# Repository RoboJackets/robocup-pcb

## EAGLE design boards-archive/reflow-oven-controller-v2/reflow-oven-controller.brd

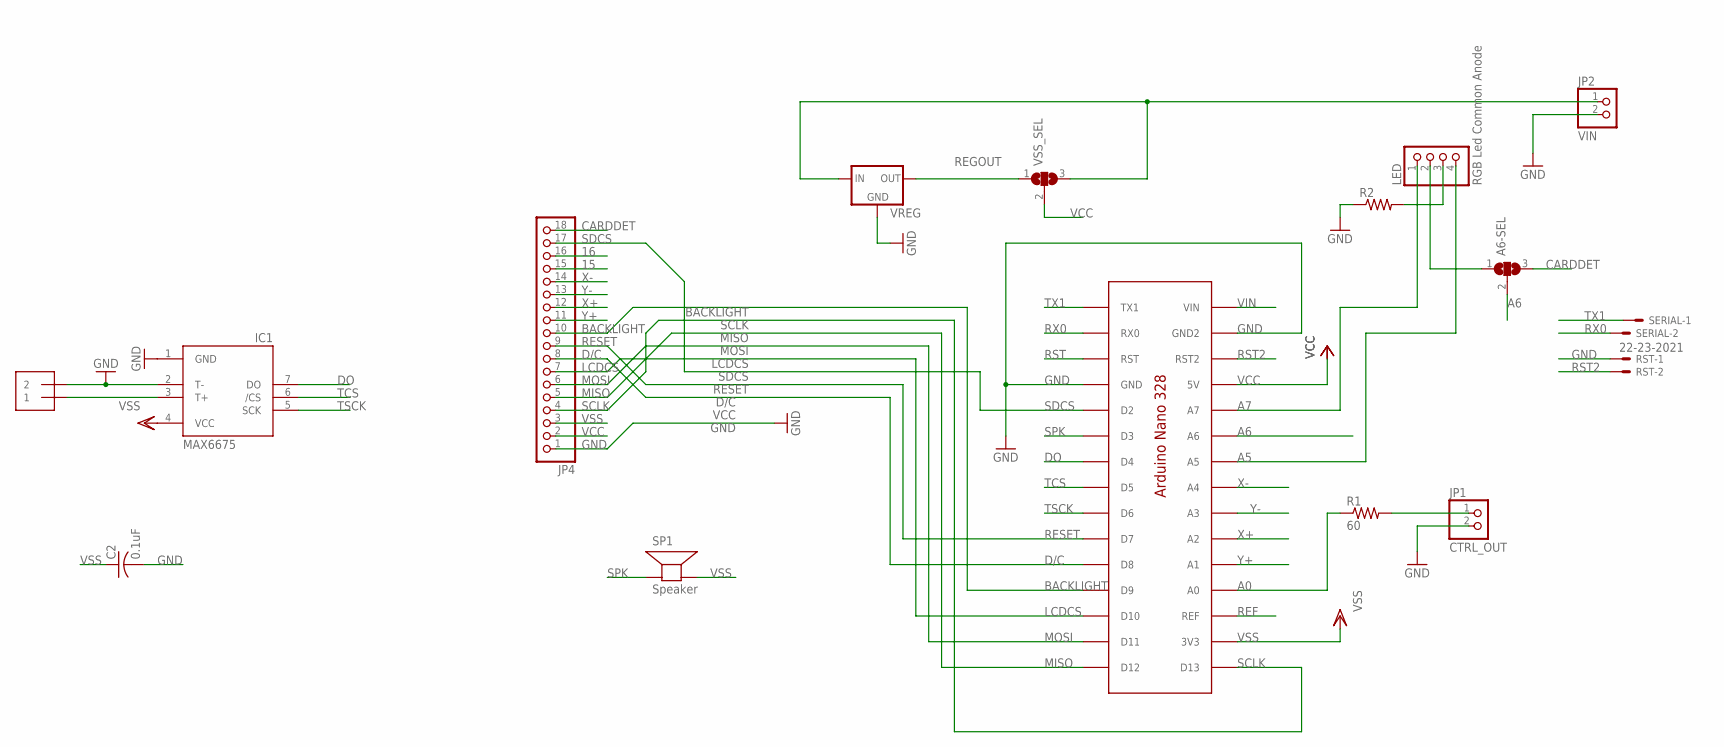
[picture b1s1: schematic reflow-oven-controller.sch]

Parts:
A6-SEL: SJ2W; SJ_2
C2: 0.1uF; C0805K
IC1: MAX6675; SO08
JP1: CTRL_OUT; 1X02/90
JP2: VIN; 1X02/90
JP4: PINHD-1X18; 1X18
LED: RGB Led Common Anode; 1X04
R1: 60; M0805
R2: R-US_R0805; R0805
RST: 22-23-2021
SERIAL: 22-23-2021
SP1: Speaker; PS12
TCOUPLE: 1X2-3.5MM; 3.5MMTERM
U$1: ANANO3.3; ANANO3.0
VREG: 78MXXS; 78SR
VSS_SEL: SJ2W; SJ_2

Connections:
15: JP4.15
16: JP4.16
A0: R1.1, U$1.A0
A5: LED.4, U$1.A5
A6: A6-SEL.2, U$1.A6
A7: LED.1, U$1.A7
BACKLIGHT: JP4.10, U$1.D9
CARDDET: A6-SEL.3, JP4.18
D/C: JP4.8, U$1.D8
DO: IC1.7 (DO), U$1.D4
GND: C2.2, IC1.1 (GND), IC1.2 (T-), JP1.2, JP2.2, JP4.1, R2.1, RST.1, TCOUPLE.2, U$1.GND, U$1.GND2, VREG.GND
LCDCS: JP4.7, U$1.D10
MISO: JP4.5, U$1.D12
MOSI: JP4.6, U$1.D11
unnamed: IC1.3 (T+), TCOUPLE.1
unnamed: A6-SEL.1, LED.2
unnamed: JP1.1, R1.2
unnamed: LED.3, R2.2
REF: U$1.REF
REGOUT: VREG.OUT, VSS_SEL.1
RESET: JP4.9, U$1.D7
RST: U$1.RST
RST2: RST.2, U$1.RST2
RX0: SERIAL.2, U$1.RX0
SCLK: JP4.4, U$1.D13
SDCS: JP4.17, U$1.D2
SPK: SP1.P$1 (+), U$1.D3
TCS: IC1.6 (/CS), U$1.D5
TRANSIN: JP2.1, VREG.IN, VSS_SEL.3
TSCK: IC1.5 (SCK), U$1.D6
TX1: SERIAL.1, U$1.TX1
VCC: JP4.2, U$1.5V, VSS_SEL.2
VIN: U$1.VIN
VSS: C2.1, IC1.4 (VCC), JP4.3, SP1.P$2 (-), U$1.3V3
X+: JP4.12, U$1.A2
X-: JP4.14, U$1.A4
Y+: JP4.11, U$1.A1
Y-: JP4.13, U$1.A3

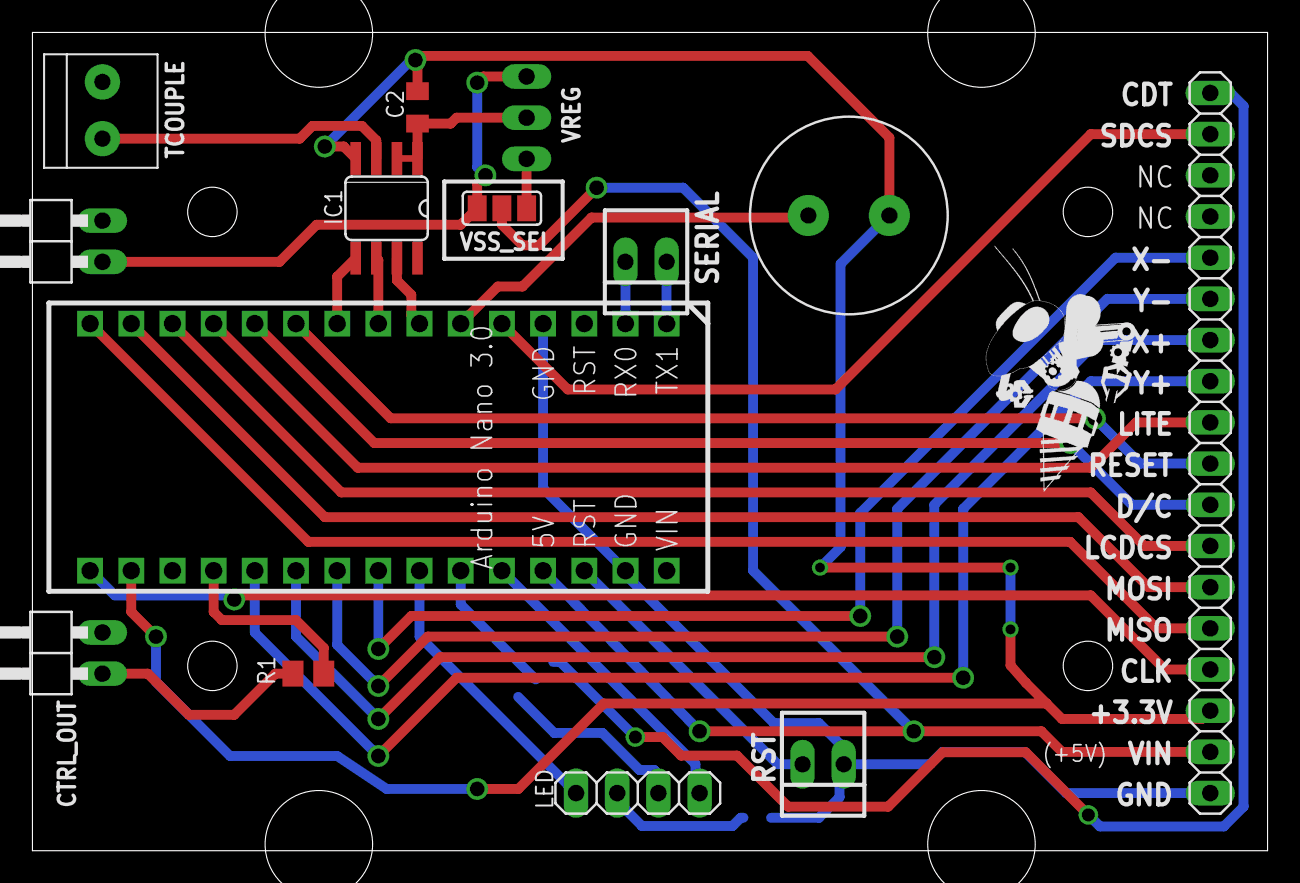
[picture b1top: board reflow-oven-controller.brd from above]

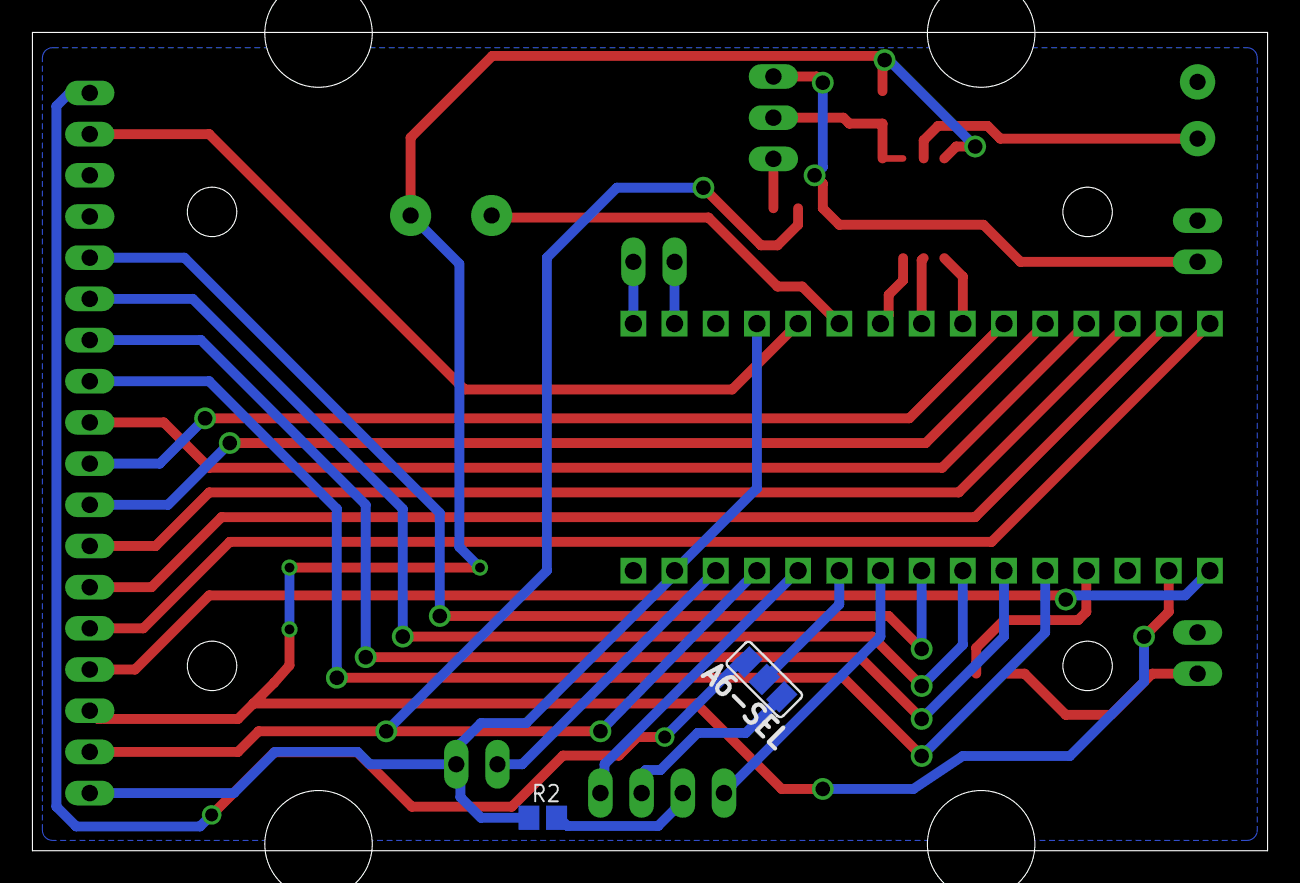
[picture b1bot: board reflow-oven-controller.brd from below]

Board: 2 copper layers, 76.2 x 50.5 mm, 17 parts (2 on the bottom side), 33 nets.

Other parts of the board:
U$2: ROBOBUZZ_0.8X

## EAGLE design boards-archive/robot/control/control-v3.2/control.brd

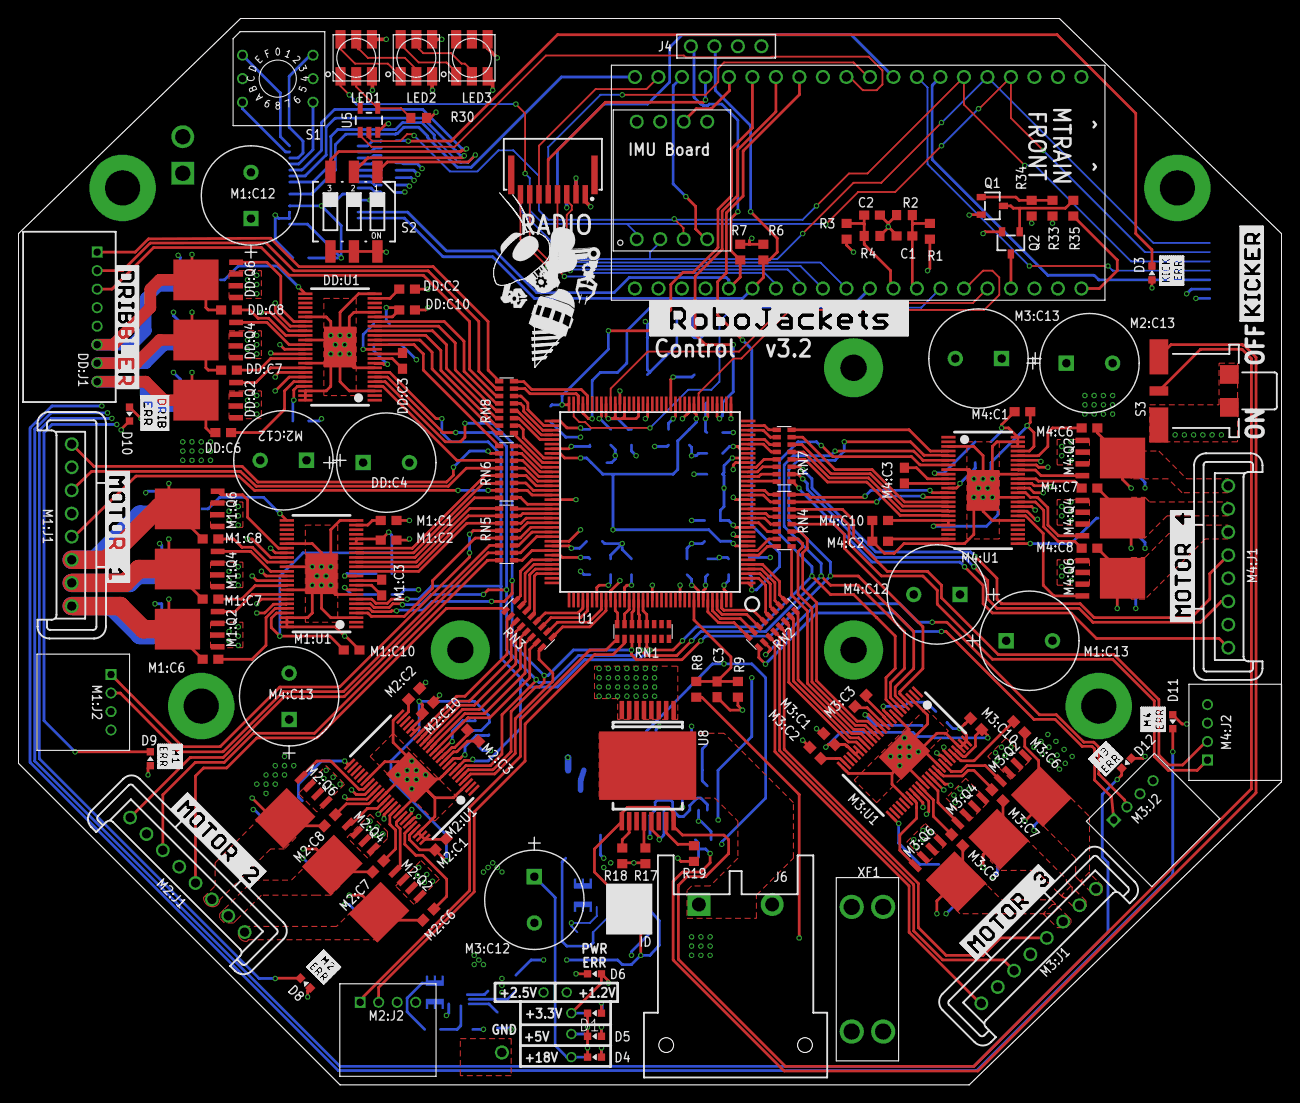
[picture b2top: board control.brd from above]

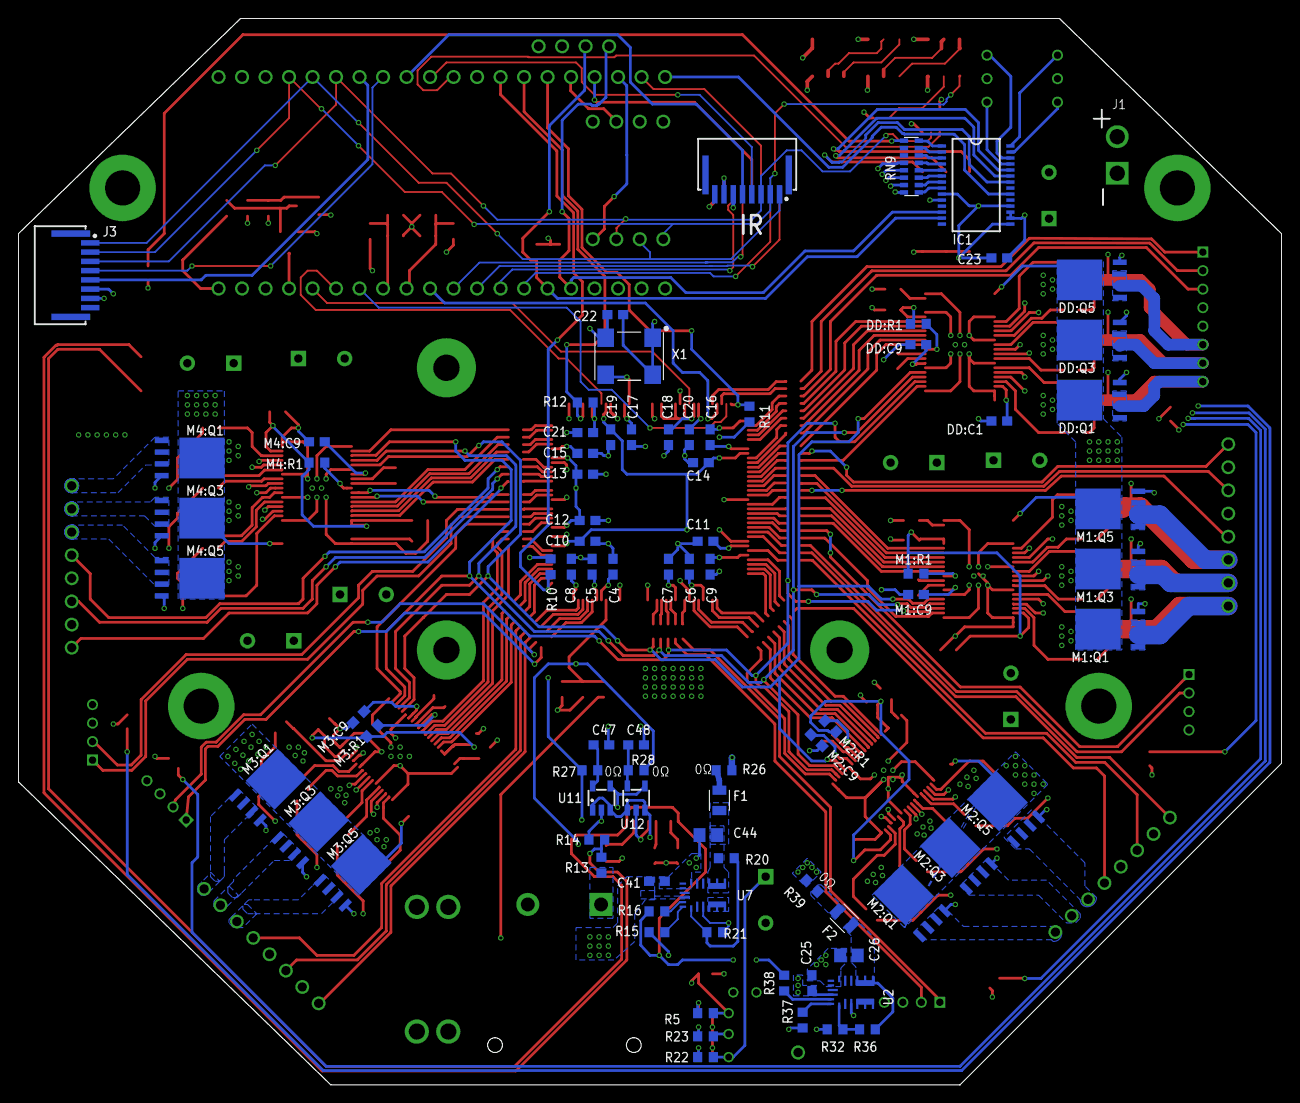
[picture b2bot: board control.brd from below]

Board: 6 copper layers, 136.5 x 115.2 mm, 223 parts (84 on the bottom side), 300 nets.

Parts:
C1: 0.1uF 50V; C0603
C2, C3, C4, C5, C6, C7, C8, C9, C10, C11, C12, C13, C14, C15, C16, C17, C18, C19, C20, C21, C22, C23: 0.1uF; C0603
C25, C41: GRM188R6YA106MA73D; C0603
C26, C44: 22uF 16V; C0805
C47, C48: 1uF; C0603
D1, D4, D5: GREEN; CHIP-LED0603
D3, D6, D8, D9, D10, D11, D12: RED; CHIP-LED0603
DD:C1, DD:C2: 1uF; C0603
DD:C3: 0.022uF 50V; C0603
DD:C4: ECA-1HHG221; CAP_PAN_10X12.5
DD:C6, DD:C7, DD:C8, DD:C10: 0.1uF 50V; C0603
DD:C9: 2.2uF 50V; C0603
DD:J1: 8-PIN_2MM-H; 2MM-8-H
DD:Q1, DD:Q2, DD:Q3, DD:Q4, DD:Q5, DD:Q6: IRFH7545; PQFN_5X6_E
DD:R1: 10k; R0603
DD:U1: DRV8303DCA; TSSOP-48_PAD
F1, F2: 0805L200SLTHYR; FUSC2113X75
IC1: MCP23017-E/SS; SSOP-28
IR: HFW8R-1ST
J1: 2-PIN-KICKERS; B2P_SMALL
J3: HFW8R-1ST
J4: 4-PIN-HEADER
J6: DF22-2; DF22-2-H
KIT1: MTRAIN; MTRAIN-KIT
KIT2: IMUIMU-KIT; IMU-KIT
LED1, LED2, LED3: APA102C-5050; APA102_5050
M1:C1, M1:C2, M2:C1, M2:C2, M3:C1, M3:C2, M4:C1, M4:C2: 1uF; C0603
M1:C3, M2:C3, M3:C3, M4:C3: 0.022uF 50V; C0603
M1:C6, M1:C7, M1:C8, M1:C10, M2:C6, M2:C7, M2:C8, M2:C10, M3:C6, M3:C7, M3:C8, M3:C10, M4:C6, M4:C7, M4:C8, M4:C10: 0.1uF 50V; C0603
M1:C9, M2:C9, M3:C9, M4:C9: 2.2uF 50V; C0603
M1:C12, M1:C13, M2:C12, M2:C13, M3:C12, M3:C13, M4:C12, M4:C13: ECA-1HHG221; CAP_PAN_10X12.5
M1:J1, M2:J1, M3:J1, M4:J1: MKS-1658
M1:J2, M2:J2, M3:J2, M4:J2: 4-PIN_2MM-H; 2MM-4-H
M1:Q1, M1:Q2, M1:Q3, M1:Q4, M1:Q5, M1:Q6, M2:Q1, M2:Q2, M2:Q3, M2:Q4, M2:Q5, M2:Q6, M3:Q1, M3:Q2, M3:Q3, M3:Q4, M3:Q5, M3:Q6, M4:Q1, M4:Q2, M4:Q3, M4:Q4, M4:Q5, M4:Q6: IRFH7545; PQFN_5X6_E
M1:R1, M2:R1, M3:R1, M4:R1: 10k; R0603
M1:U1, M2:U1, M3:U1, M4:U1: DRV8303DCA; TSSOP-48_PAD
Q1, Q2: BSS806NH6327XTSA1; SOT-23-3
R1: 68k 1%; R0603
R2, R3, R4: 10k 1%; R0603
R5, R18, R19, R22, R23: 1k; R0603
R6, R7, R10, R12: 4.7k; R0603
R8: 68k; R0603
R9, R17, R33: 10k; R0603
R11: 330; R0603
R13: 270k; R0603
R14, R34, R35: 100k; R0603
R15: 43.2k; R0603
R16, R38: 150k; R0603
R20, R36: 160k 1%; R0603
R21: 30.1k 1%; R0603
R26, R27, R28, R39: 0; R0603
R30: 50k; R0603
R32: 51.0k 1%; R0603
R37: 29.4k; R0603
RADIO: HFW8R-1ST
RN1, RN2, RN3, RN4, RN5, RN6, RN7, RN8, RN9: 330; RA-8_2506
S1: 94HCB16T; HEX
S2: 219-03; CTS-219-03
S3: 34EWMSP12M6RT
U1: XC3S250E-4TQG144C; TQFP144
U2, U7: MPM3620GQV-P
U5: SN74AHC1G125; SOT23-5
U8: VND5E006ASPTR-E; POWERSO-16
U11: MCP1824T-1202E/OT; SOT-23-5
U12: MCP1824T-2502E/OT; SOT-23-5
U$1: ERR-DRIB
U$2: ROBOJACKETS
U$3: MOTOR-1
U$4: DRIBBLER
U$5: MOTOR-2
U$6: MOTOR-3
U$7: MOTOR-4
U$8: ERR-M1
U$9: KICKER
U$11: ROBOBUZZ_1.0X2
U$12: ERR-M2
U$13: ERR-M3
U$14: ERR-M4
U$15: ERR-KICK
X1: ASV-18.432MHZ-EJ-T; ASV
XF1: 30A; 3557-2

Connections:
5V-LED: D5.A, R23.2
5V-LED1: D1.A, R5.2
18.5V-LED: D4.A, R22.1
!CS!-DOT: KIT1.P$11, U5.1
!CS!-FPGA: KIT1.P$31, U1.69
!CS!-ICM: KIT1.P$18, KIT2.4
!CS!-IR: IR.4, KIT1.P$10
!CS!-KICK: J3.4, KIT1.P$8
!CS!-RAD0: KIT1.P$17, RADIO.5
!RST!-IR: IR.5, KIT1.P$9
!RST!-KICK: J3.5, KIT1.P$7
!RST!-NETWORK: KIT1.!RST, Q2.3
!RST!-RADIO: KIT1.P$19, RADIO.6
!RST!_CTRL: Q1.3, Q2.1, R35.1
+1.2V: C6.1, C10.1, C14.1, C19.1, R27.2, U1.9, U1.45, U1.80, U1.115
+1.2V-PRE: C47.1, R27.1, U11.5
+2.5V: C4.1, C9.1, C15.1, C20.1, R10.2, R11.2, R28.2, U1.30, U1.65, U1.102, U1.137
+2.5V-PRE: C48.1, R28.1, U12.5
+3.3V: C5.1, C7.1, C8.1, C11.1, C12.1, C13.1, C16.1, C17.1, C18.1, C21.1, C22.1, C23.1, D3.A, D6.A, D8.A, D9.A, D10.A, D11.A, D12.A, DD:C1.1, DD:C10.1, DD:R1.1, DD:U1.19, DD:U1.45, IC1.9, IC1.15, IC1.18, IR.6, J3.7, J4.2, KIT2.8, R5.1, R6.2, R7.2, R12.1, R33.2, R39.2, U1.13, U1.28, U1.42, U1.49, U1.57, U1.60, U1.62, U1.64, U1.79, U1.100, U1.121, U1.138, U1.143, U5.5, U11.1, U11.3, U12.1, U12.3, X1.1, X1.4
+3.3V-FUSE: C26.1, F2.1, R36.2, U2.789
+5V: DD:J1.5, KIT1.VIN, LED1.1, LED2.1, LED3.1, M1:J1.4, M1:J2.4, M2:J1.4, M2:J2.4, M3:J1.4, M3:J2.4, M4:J1.4, M4:J2.4, R3.1, R23.1, R26.2, RADIO.1
+5V-FUSE: C44.1, F1.1, R20.2, U7.789
+18.5V: C25.1, C41.1, DD:C4.1, DD:Q1.5678, DD:Q3.5678, DD:Q5.5678, DD:U1.25, M1:C12.1, M1:C13.1, M1:Q1.5678, M1:Q3.5678, M1:Q5.5678, M1:U1.25, M2:C12.1, M2:C13.1, M2:Q1.5678, M2:Q3.5678, M2:Q5.5678, M2:U1.25, M3:C12.1, M3:C13.1, M3:Q1.5678, M3:Q3.5678, M3:Q5.5678, M3:U1.25, M4:C12.1, M4:C13.1, M4:Q1.5678, M4:Q3.5678, M4:Q5.5678, M4:U1.25, R1.1, R8.1, R22.2, U2.16, U7.16, XF1.3, XF1.4
AAM: R15.2, U7.18
AAM1: R37.2, U2.18
BATT-FPGA: C3.1, R8.2, R9.1, U1.136
BATT_PWR_AVAIL: Q1.1, R33.1, R34.2
CS1: R18.2, U8.10
CS2: R19.2, U8.15
CS-DIS: R17.2, U8.12
DD-!CS: DD:U1.4, RN6.11
DD-A-H: DD:U1.13, RN6.9
DD-A-L: DD:U1.14, RN8.16
DD-B-H: DD:U1.15, RN8.15
DD-B-L: DD:U1.16, RN8.14
DD-C-H: DD:U1.17, RN8.13
DD-C-L: DD:U1.18, RN8.12
DD-H1: DD:J1.3, RN8.11
DD-H2: DD:J1.2, RN8.10
DD-H3: DD:J1.1, RN8.9
DD:AVDD: DD:C2.1, DD:U1.23
DD:BST-A: DD:C6.1, DD:U1.44
DD:BST-B: DD:C7.1, DD:U1.39
DD:BST-C: DD:C8.1, DD:U1.34
DD:CP1: DD:C3.1, DD:U1.10
DD:CP2: DD:C3.2, DD:U1.11
DD:EN-GATE: DD:R1.2, DD:U1.12
DD:GH-A: DD:Q1.4, DD:U1.43
DD:GH-B: DD:Q3.4, DD:U1.38
DD:GH-C: DD:Q5.4, DD:U1.33
DD:GL-A: DD:Q2.4, DD:U1.41
DD:GL-B: DD:Q4.4, DD:U1.36
DD:GL-C: DD:Q6.4, DD:U1.31
DD:GVDD: DD:C9.1, DD:U1.9
DD:PHASE-A: DD:C6.2, DD:J1.8, DD:Q1.1, DD:Q1.2, DD:Q1.3, DD:Q2.5678, DD:U1.42
DD:PHASE-B: DD:C7.2, DD:J1.7, DD:Q3.1, DD:Q3.2, DD:Q3.3, DD:Q4.5678, DD:U1.37
DD:PHASE-C: DD:C8.2, DD:J1.6, DD:Q5.1, DD:Q5.2, DD:Q5.3, DD:Q6.5678, DD:U1.32
DIP-1: IC1.22, S2.1
DIP-2: IC1.23, S2.2
DIP-3: IC1.24, S2.3
DOT-CLK-1: LED1.5, R30.2, U5.4
DOT-CLK-1-2: LED1.2, LED2.5
DOT-CLK-2-3: LED2.2, LED3.5
DOT-MOSI-1-2: LED1.3, LED2.4
DOT-MOSI-2-3: LED2.3, LED3.4
EN: R16.2, U7.17
EN1: R38.2, U2.17
EN-PWR: R16.1, R38.1, S3.2, U8.9, U8.16
EN-PWR-PRE: R13.1, R14.2, S3.1
FB: R20.1, R21.2, U7.1
FB1: R32.2, R36.1, U2.1
FPGA-CLK: U1.50, X1.3
FPGA-DONE: KIT1.P$15, R11.1, U1.72
FPGA-INIT: KIT1.P$14, R12.2, U1.40
FPGA-PROG: KIT1.P$13, R10.1, U1.1
GND: C1.2, C2.2, C3.2, C4.2, C5.2, C6.2, C7.2, C8.2, C9.2, C10.2, C11.2, C12.2, C13.2, C14.2, C15.2, C16.2, C17.2, C18.2, C19.2, C20.2, C21.2, C22.2, C23.2, C25.2, C26.2, C41.2, C44.2, C47.2, C48.2, D1.C, D4.C, D5.C, DD:C1.2, DD:C2.2, DD:C4.2, DD:C9.2, DD:C10.2, DD:J1.4, DD:Q2.1, DD:Q2.2, DD:Q2.3, DD:Q4.1, DD:Q4.2, DD:Q4.3, DD:Q6.1, DD:Q6.2, DD:Q6.3, DD:U1.3, DD:U1.8, DD:U1.20, DD:U1.24, DD:U1.30, DD:U1.35, DD:U1.40, DD:U1.46, DD:U1.47, DD:U1.48, DD:U1.PAD, IC1.10, IC1.16, IC1.17, IR.7, J1.1, J3.6, J4.1, J6.2, KIT1.GND, KIT2.5, LED1.6, LED2.6, LED3.6, M1:C1.2, M1:C2.2, M1:C9.2, M1:C10.2, M1:C12.2, M1:C13.2, M1:J1.2, M1:J2.3, M1:Q2.1, M1:Q2.2, M1:Q2.3, M1:Q4.1, M1:Q4.2, M1:Q4.3, M1:Q6.1, M1:Q6.2, M1:Q6.3, M1:U1.3, M1:U1.8, M1:U1.24, M1:U1.30, M1:U1.35, M1:U1.40, M1:U1.46, M1:U1.47, M1:U1.48, M1:U1.PAD, M2:C1.2, M2:C2.2, M2:C9.2, M2:C10.2, M2:C12.2, M2:C13.2, M2:J1.2, M2:J2.3, M2:Q2.1, M2:Q2.2, M2:Q2.3, M2:Q4.1, M2:Q4.2, M2:Q4.3, M2:Q6.1, M2:Q6.2, M2:Q6.3, M2:U1.3, M2:U1.8, M2:U1.24, M2:U1.30, M2:U1.35, M2:U1.40, M2:U1.46, M2:U1.47, M2:U1.48, M2:U1.PAD, M3:C1.2, M3:C2.2, M3:C9.2, M3:C10.2, M3:C12.2, M3:C13.2, M3:J1.2, M3:J2.3, M3:Q2.1, M3:Q2.2, M3:Q2.3, M3:Q4.1, M3:Q4.2, M3:Q4.3, M3:Q6.1, M3:Q6.2, M3:Q6.3, M3:U1.3, M3:U1.8, M3:U1.24, M3:U1.30, M3:U1.35, M3:U1.40, M3:U1.46, M3:U1.47, M3:U1.48, M3:U1.PAD, M4:C1.2, M4:C2.2, M4:C9.2, M4:C10.2, M4:C12.2, M4:C13.2, M4:J1.2, M4:J2.3, M4:Q2.1, M4:Q2.2, M4:Q2.3, M4:Q4.1, M4:Q4.2, M4:Q4.3, M4:Q6.1, M4:Q6.2, M4:Q6.3, M4:U1.3, M4:U1.8, M4:U1.24, M4:U1.30, M4:U1.35, M4:U1.40, M4:U1.46, M4:U1.47, M4:U1.48, M4:U1.PAD, Q1.2, Q2.2, R2.2, R4.2, R9.2, R14.1, R15.1, R17.1, R18.1, R19.1, R21.1, R30.1, R32.1, R34.1, R37.1, RADIO.2, S1.C1, S1.C2, S2.4, S2.5, S2.6, S3.3, S3.LEG1, S3.LEG3, U1.11, U1.19, U1.27, U1.37, U1.46, U1.55, U1.61, U1.73, U1.90, U1.99, U1.118, U1.127, U1.133, U2.3, U2.12, U2.13, U2.14, U5.3, U7.3, U7.12, U7.13, U7.14, U8.13, U11.2, U12.2, X1.2
GPB0: IC1.1, RN9.8
GPB1: IC1.2, RN9.7
GPB2: IC1.3, RN9.6
GPB3: IC1.4, RN9.5
GPB4: IC1.5, RN9.4
GPB5: IC1.6, RN9.3
GPB6: IC1.7, RN9.2
GPB7: IC1.8, RN9.1
HEX-0: IC1.28, S1.1
HEX-1: IC1.25, S1.2
HEX-2: IC1.27, S1.4
HEX-3: IC1.26, S1.8
INT-ICM: KIT1.P$16, KIT2.6
INT-IO: IC1.20, KIT1.P$20
INT-RAD0: KIT1.P$30, RADIO.4
LED-DD: D10.C, RN9.16
LED-KICK: D3.C, RN9.9
LED-M1: D9.C, RN9.15
LED-M2: D8.C, RN9.14
LED-M3: D12.C, RN9.13
LED-M4: D11.C, RN9.12
M1-!CS: M1:U1.4, RN5.13
M1-A-H: M1:U1.15, RN5.9
M1-A-L: M1:U1.16, RN6.16
M1-B-H: M1:U1.13, RN5.11
M1-B-L: M1:U1.14, RN5.10
M1-C-H: M1:U1.17, RN6.14
M1-C-L: M1:U1.18, RN6.13
M1-ENC-A: M1:J2.2, RN5.14
M1-ENC-B: M1:J2.1, RN5.12
M1-H1: M1:J1.1, RN6.10
M1-H2: M1:J1.3, RN6.12
M1-H3: M1:J1.5, RN6.15
M1:+3.3V: M1:C1.1, M1:C10.1, M1:R1.1, M1:U1.19, M1:U1.20, M1:U1.45
M1:AVDD: M1:C2.1, M1:U1.23
M1:BST-A: M1:C6.1, M1:U1.44
M1:BST-B: M1:C7.1, M1:U1.39
M1:BST-C: M1:C8.1, M1:U1.34
M1:CP1: M1:C3.1, M1:U1.10
M1:CP2: M1:C3.2, M1:U1.11
M1:EN-GATE: M1:R1.2, M1:U1.12
M1:GH-A: M1:Q1.4, M1:U1.43
M1:GH-B: M1:Q3.4, M1:U1.38
M1:GH-C: M1:Q5.4, M1:U1.33
M1:GL-A: M1:Q2.4, M1:U1.41
M1:GL-B: M1:Q4.4, M1:U1.36
M1:GL-C: M1:Q6.4, M1:U1.31
M1:GVDD: M1:C9.1, M1:U1.9
M1:PHASE-A: M1:C7.2, M1:J1.7, M1:Q3.1, M1:Q3.2, M1:Q3.3, M1:Q4.5678, M1:U1.37
M1:PHASE-B: M1:C6.2, M1:J1.8, M1:Q1.1, M1:Q1.2, M1:Q1.3, M1:Q2.5678, M1:U1.42
M1:PHASE-C: M1:C8.2, M1:J1.6, M1:Q5.1, M1:Q5.2, M1:Q5.3, M1:Q6.5678, M1:U1.32
M2-!CS: M2:U1.4, RN3.16
M2-A-H: M2:U1.15, RN3.13
M2-A-L: M2:U1.16, RN3.12
M2-B-H: M2:U1.13, RN3.15
M2-B-L: M2:U1.14, RN3.14
M2-C-H: M2:U1.17, RN3.11
M2-C-L: M2:U1.18, RN3.10
M2-ENC-A: M2:J2.2, RN1.10
M2-ENC-B: M2:J2.1, RN1.9
M2-H1: M2:J1.1, RN5.15
M2-H2: M2:J1.3, RN5.16
M2-H3: M2:J1.5, RN3.9
M2:+3.3V: M2:C1.1, M2:C10.1, M2:R1.1, M2:U1.19, M2:U1.20, M2:U1.45
M2:AVDD: M2:C2.1, M2:U1.23
M2:BST-A: M2:C6.1, M2:U1.44
M2:BST-B: M2:C7.1, M2:U1.39
M2:BST-C: M2:C8.1, M2:U1.34
M2:CP1: M2:C3.1, M2:U1.10
M2:CP2: M2:C3.2, M2:U1.11
M2:EN-GATE: M2:R1.2, M2:U1.12
M2:GH-A: M2:Q1.4, M2:U1.43
M2:GH-B: M2:Q3.4, M2:U1.38
M2:GH-C: M2:Q5.4, M2:U1.33
M2:GL-A: M2:Q2.4, M2:U1.41
M2:GL-B: M2:Q4.4, M2:U1.36
M2:GL-C: M2:Q6.4, M2:U1.31
M2:GVDD: M2:C9.1, M2:U1.9
M2:PHASE-A: M2:C7.2, M2:J1.7, M2:Q3.1, M2:Q3.2, M2:Q3.3, M2:Q4.5678, M2:U1.37
M2:PHASE-B: M2:C6.2, M2:J1.8, M2:Q1.1, M2:Q1.2, M2:Q1.3, M2:Q2.5678, M2:U1.42
M2:PHASE-C: M2:C8.2, M2:J1.6, M2:Q5.1, M2:Q5.2, M2:Q5.3, M2:Q6.5678, M2:U1.32
M3-!CS: M3:U1.4, RN4.12
M3-A-H: M3:U1.15, RN4.9
M3-A-L: M3:U1.16, RN2.16
M3-B-H: M3:U1.13, RN4.11
M3-B-L: M3:U1.14, RN4.10
M3-C-H: M3:U1.17, RN2.15
M3-C-L: M3:U1.18, RN2.14
M3-ENC-A: M3:J2.2, RN2.10
M3-ENC-B: M3:J2.1, RN2.9
M3-H1: M3:J1.1, RN2.11
M3-H2: M3:J1.3, RN2.12
M3-H3: M3:J1.5, RN2.13
M3:+3.3V: M3:C1.1, M3:C10.1, M3:R1.1, M3:U1.19, M3:U1.20, M3:U1.45
M3:AVDD: M3:C2.1, M3:U1.23
M3:BST-A: M3:C6.1, M3:U1.44
M3:BST-B: M3:C7.1, M3:U1.39
M3:BST-C: M3:C8.1, M3:U1.34
M3:CP1: M3:C3.1, M3:U1.10
M3:CP2: M3:C3.2, M3:U1.11
M3:EN-GATE: M3:R1.2, M3:U1.12
M3:GH-A: M3:Q1.4, M3:U1.43
M3:GH-B: M3:Q3.4, M3:U1.38
M3:GH-C: M3:Q5.4, M3:U1.33
M3:GL-A: M3:Q2.4, M3:U1.41
M3:GL-B: M3:Q4.4, M3:U1.36
M3:GL-C: M3:Q6.4, M3:U1.31
M3:GVDD: M3:C9.1, M3:U1.9
M3:PHASE-A: M3:C7.2, M3:J1.7, M3:Q3.1, M3:Q3.2, M3:Q3.3, M3:Q4.5678, M3:U1.37
M3:PHASE-B: M3:C6.2, M3:J1.8, M3:Q1.1, M3:Q1.2, M3:Q1.3, M3:Q2.5678, M3:U1.42
M3:PHASE-C: M3:C8.2, M3:J1.6, M3:Q5.1, M3:Q5.2, M3:Q5.3, M3:Q6.5678, M3:U1.32
M4-!CS: M4:U1.4, RN7.16
M4-A-H: M4:U1.15, RN7.15
M4-A-L: M4:U1.16, RN7.14
M4-B-H: M4:U1.13, RN4.16
M4-B-L: M4:U1.14, RN4.15
M4-C-H: M4:U1.17, RN7.13
M4-C-L: M4:U1.18, RN7.12
M4-ENC-A: M4:J2.2, RN4.14
M4-ENC-B: M4:J2.1, RN4.13
M4-H1: M4:J1.1, RN7.9
M4-H2: M4:J1.3, RN7.10
M4-H3: M4:J1.5, RN7.11
M4:+3.3V: M4:C1.1, M4:C10.1, M4:R1.1, M4:U1.19, M4:U1.20, M4:U1.45
M4:AVDD: M4:C2.1, M4:U1.23
M4:BST-A: M4:C6.1, M4:U1.44
M4:BST-B: M4:C7.1, M4:U1.39
M4:BST-C: M4:C8.1, M4:U1.34
M4:CP1: M4:C3.1, M4:U1.10
M4:CP2: M4:C3.2, M4:U1.11
M4:EN-GATE: M4:R1.2, M4:U1.12
M4:GH-A: M4:Q1.4, M4:U1.43
M4:GH-B: M4:Q3.4, M4:U1.38
M4:GH-C: M4:Q5.4, M4:U1.33
M4:GL-A: M4:Q2.4, M4:U1.41
M4:GL-B: M4:Q4.4, M4:U1.36
M4:GL-C: M4:Q6.4, M4:U1.31
M4:GVDD: M4:C9.1, M4:U1.9
M4:PHASE-A: M4:C7.2, M4:J1.7, M4:Q3.1, M4:Q3.2, M4:Q3.3, M4:Q4.5678, M4:U1.37
M4:PHASE-B: M4:C6.2, M4:J1.8, M4:Q1.1, M4:Q1.2, M4:Q1.3, M4:Q2.5678, M4:U1.42
M4:PHASE-C: M4:C8.2, M4:J1.6, M4:Q5.1, M4:Q5.2, M4:Q5.3, M4:Q6.5678, M4:U1.32
MISO: IR.1, J3.1, KIT1.P$5, KIT2.2
MISO-AUX: DD:U1.6, M1:U1.6, M2:U1.6, M3:U1.6, M4:U1.6, RN1.12
MISO-FPGA: KIT1.P$35, U1.44
MISO-RADIO: KIT1.P$28, RADIO.3
MOSI: IR.2, J3.2, KIT1.P$4, KIT2.1, LED1.4
MOSI-AUX: DD:U1.5, M1:U1.5, M2:U1.5, M3:U1.5, M4:U1.5, RN1.11
MOSI-FPGA: KIT1.P$36, U1.63
MOSI-RADIO: KIT1.P$27, RADIO.7
unnamed: F2.2, R39.1
unnamed: F1.2, R26.1
PWR-ERR: D6.C, U11.4, U12.4
R-P1: RN8.1, U1.82
R-P2: RN8.2, U1.81
R-P3: RN8.3, U1.77
R-P4: RN8.4, U1.76
R-P5: RN8.5, U1.75
R-P6: RN8.6, U1.74
R-P7: RN8.7, U1.70
R-P8: RN8.8, U1.68
R-P9: RN6.1, U1.91
R-P10: RN6.2, U1.89
R-P11: RN6.3, U1.88
R-P12: RN6.4, U1.87
R-P13: RN6.5, U1.86
R-P14: RN6.6, U1.85
R-P15: RN6.7, U1.84
R-P16: RN6.8, U1.83
R-P17: RN5.1, U1.101
R-P18: RN5.2, U1.98
R-P19: RN5.3, U1.97
R-P20: RN5.4, U1.96
R-P21: RN5.5, U1.95
R-P22: RN5.6, U1.94
R-P23: RN5.7, U1.93
R-P24: RN5.8, U1.92
R-P25: RN3.1, U1.117
R-P26: RN3.2, U1.116
R-P27: RN3.3, U1.113
R-P28: RN3.4, U1.112
R-P29: RN3.5, U1.106
R-P30: RN3.6, U1.105
R-P31: RN3.7, U1.104
R-P32: RN3.8, U1.103
R-P36: RN1.4, U1.125
R-P37: RN1.5, U1.124
R-P38: RN1.6, U1.123
R-P39: RN1.7, U1.122
R-P40: RN1.8, U1.119
R-P41: RN2.1, U1.5
R-P42: RN2.2, U1.4
R-P43: RN2.3, U1.3
R-P44: RN2.4, U1.2
R-P45: RN2.5, U1.142
R-P46: RN2.6, U1.141
R-P47: RN2.7, U1.140
R-P48: RN2.8, U1.139
R-P49: RN4.1, U1.21
R-P50: RN4.2, U1.20
R-P51: RN4.3, U1.17
R-P52: RN4.4, U1.16
R-P53: RN4.5, U1.15
R-P54: RN4.6, U1.14
R-P55: RN4.7, U1.8
R-P56: RN4.8, U1.7
R-P57: RN7.1, U1.35
R-P58: RN7.2, U1.34
R-P59: RN7.3, U1.32
R-P60: RN7.4, U1.31
R-P61: RN7.5, U1.26
R-P62: RN7.6, U1.25
R-P63: RN7.7, U1.24
R-P64: RN7.8, U1.23
SCK: IR.3, J3.3, KIT1.P$6, KIT2.3, U5.2
SCK-AUX: DD:U1.7, M1:U1.7, M2:U1.7, M3:U1.7, M4:U1.7, RN1.13
SCK-FPGA: KIT1.P$34, U1.71
SCK-RADIO: KIT1.P$29, RADIO.8
SCL: IC1.12, J4.4, KIT1.P$25, R7.1
SDA: IC1.13, J4.3, KIT1.P$26, R6.1
SENSE-BATT: C1.1, KIT1.P$33, R1.2, R2.1
SENSE-VIN: C2.1, KIT1.P$32, R3.2, R4.1
VBATT: J1.2, U8.1, U8.2, U8.3, U8.4, U8.5, U8.6, U8.7, U8.8, XF1.1, XF1.2
VIN: J6.1, R13.2, U8.17
V_MTRAIN: KIT1.VDD, R35.2

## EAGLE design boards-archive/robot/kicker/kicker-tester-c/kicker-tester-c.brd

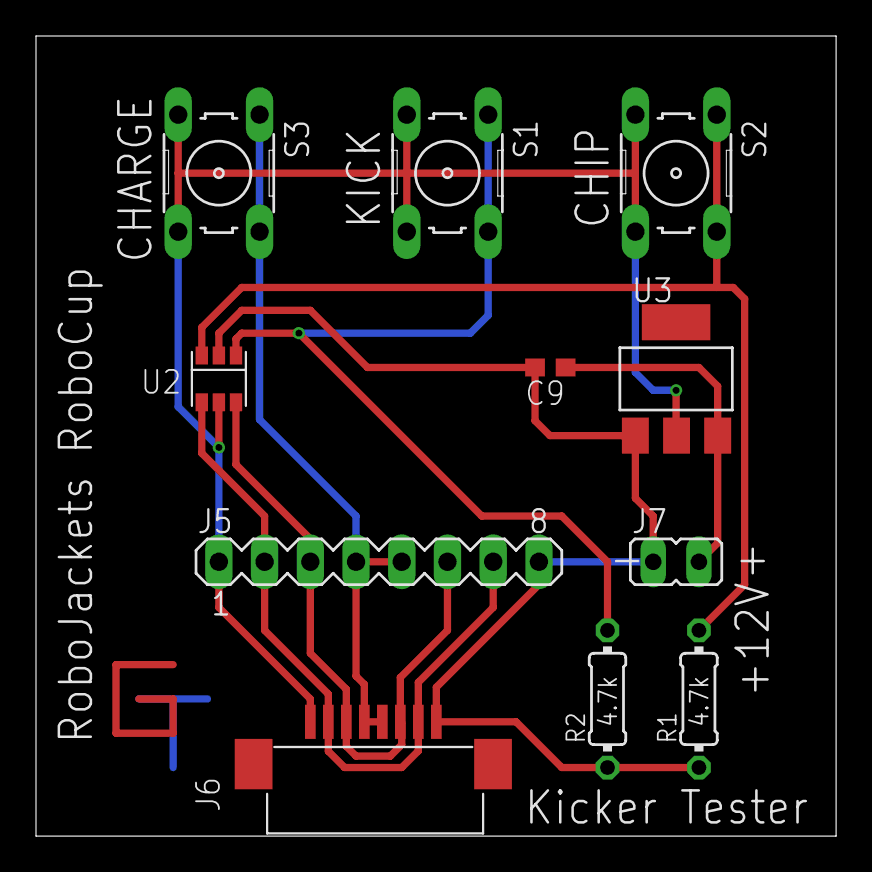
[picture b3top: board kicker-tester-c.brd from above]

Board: 2 copper layers, 44.5 x 44.5 mm, 11 parts (0 on the bottom side), 8 nets.

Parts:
C9: 100nF; C0603
J5: MA08-1
J6: 0528520870
J7: JP1
R1, R2: 4.7k; 0204/7
S1, S2, S3: B3F-10XX
U2: MAX6817; SOT23-6
U3: REG1117; SOT223

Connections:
unnamed: R2.2, S1.1, S1.2, U2.1
unnamed: R1.2, S2.1, S2.2, U2.3
TEST_CHARGE: J5.4, J5.5, J6.4, J6.5, S3.1, S3.2
TEST_CHIP: J5.2, J5.7, J6.2, J6.7, U2.4
TEST_GND: C9.2, J5.8, J6.8, J7.1, R1.1, R2.1, U2.2, U3.1
TEST_KICK: J5.3, J5.6, J6.3, J6.6, U2.6
TEST_VBATT: C9.1, J7.2, U3.3
TEST_VCC: J5.1, J6.1, S1.3, S1.4, S2.3, S2.4, S3.3, S3.4, U2.5, U3.2

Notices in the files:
parts and their libraries:
SparkFun-IC-Logic: Licensing: Creative Commons ShareAlike 4.0 International - https://creativecommons.org/licenses/by-sa/4.0
